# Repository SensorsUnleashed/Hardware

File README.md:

# Sensors unleashed Hardware

This repository will hold all the hardware for the sensors unleashed project.
All repositories will be placed here as submodules, which you can request
by a simple command:

git submodule update --init submoduleName

e.g.
git submodule update --init zb3219PA_XBEEAdapter

or for all submodules in the repo do:
git submodule update --init

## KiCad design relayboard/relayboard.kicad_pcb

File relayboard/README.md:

# relayboard

Simple board that is powered by both mains and a button cell battery.

It is able to:
* Operate a Single Pole Double Throw relay
* Has an i2c eeprom
* Can attach to a Sensors Unleashed radio module
* If mains is lost, the relay will release, but the radio will still be operating. This means that messages can still be send even though power is removed.

This board has many uses, but some ideas could be:
Use any installation in the house as input for the system. This device will detect if mains is on or off, and send messages as instructed. Perhaps turning on/off lamps or plugs in another location in a house.

The relay can be used to switch anything - lights, pumps, home appliances and so on.

Below you can see the prototype board.

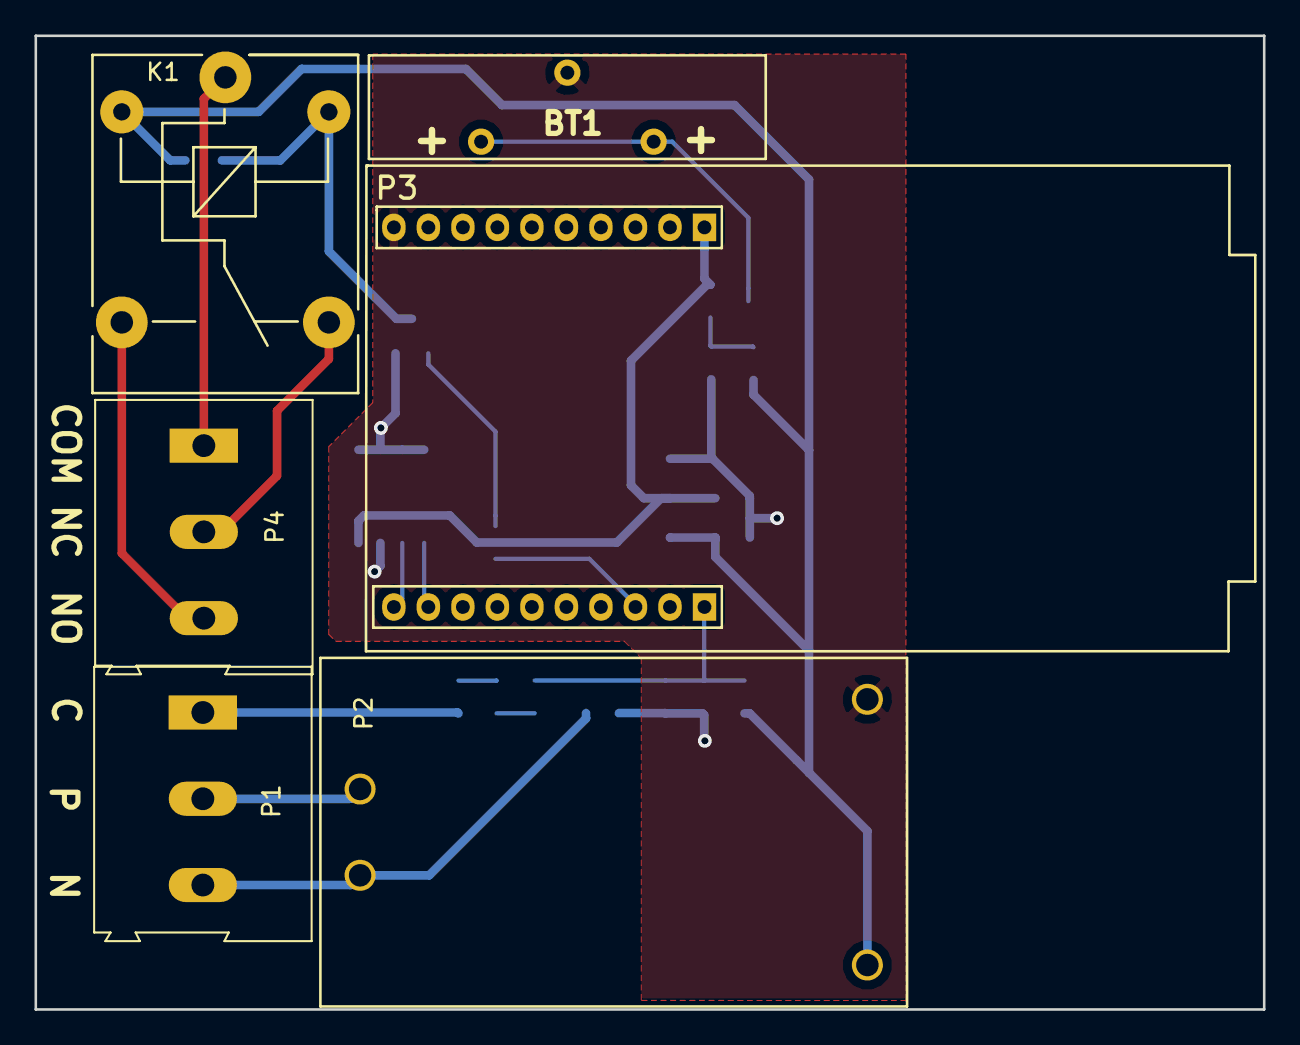
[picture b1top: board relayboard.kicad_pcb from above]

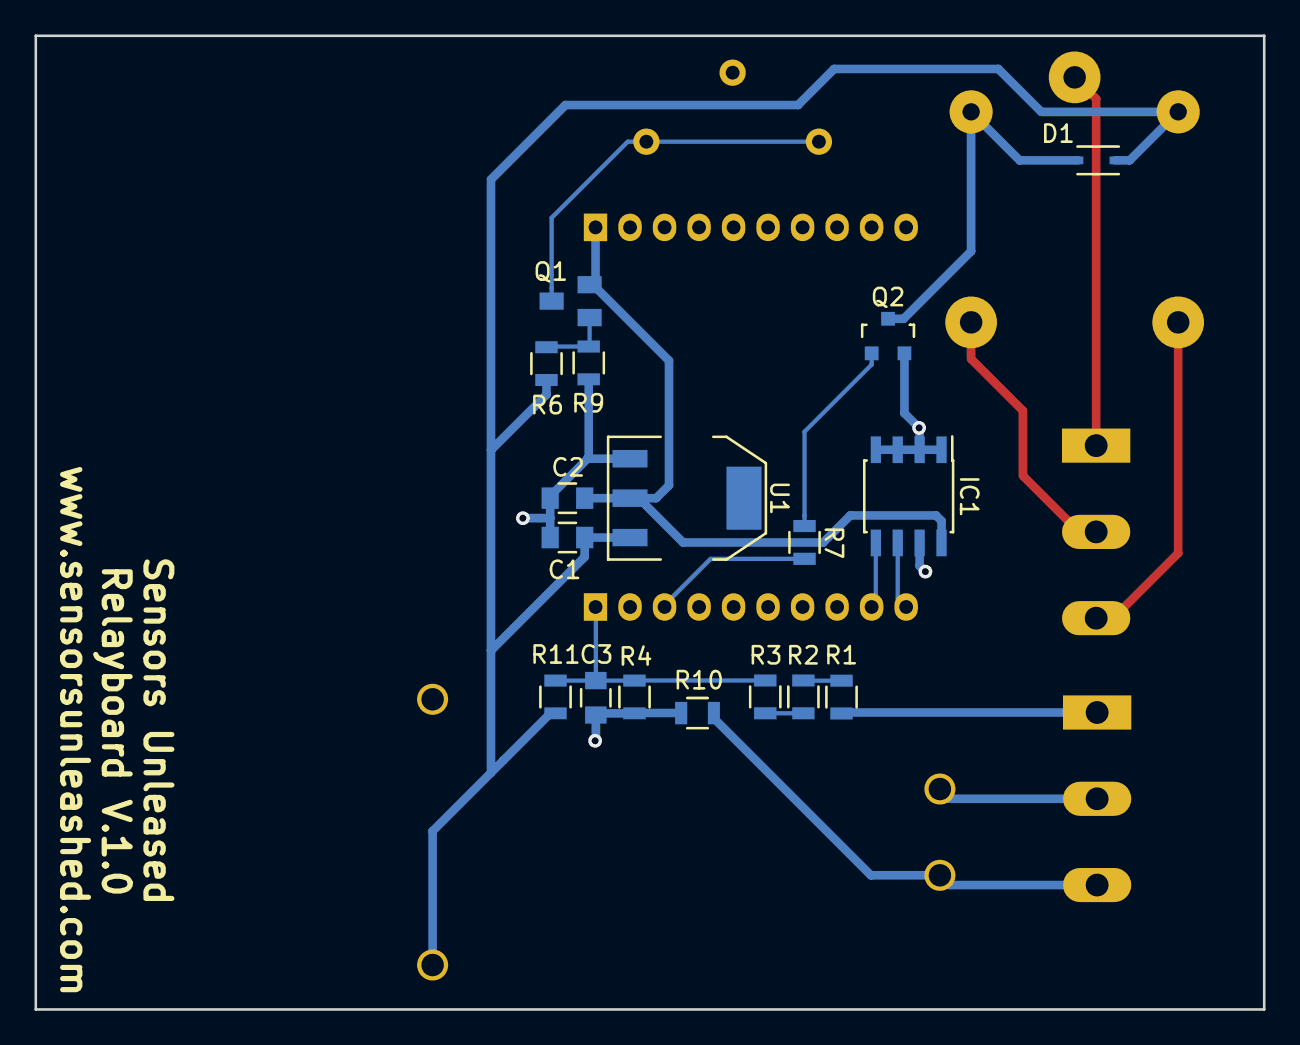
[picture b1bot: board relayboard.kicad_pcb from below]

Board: 2 copper layers, 71.2 x 56.4 mm, 23 parts (17 on the bottom side), 19 nets.

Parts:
BT1: CR2032; BATT_CR2032_VERT
C1: 100nF; C_0805
C2: 22uF; C_0805
C3: 1nF; C_0805
D1: BAS321; SOD-323
IC1: AT24C256C-SSHL-T; SOIC-8_3.9x4.9mm_Pitch1.27mm
K1: RELAY_1RT; Relay_SRD_XVDC-SL-C_Series
P1: Supply; AK300-3
P2: HLK-PM01
P3: Sensors Unleashed Radio; zb3219PA_radio
P4: Relay; AK300-3
Q1: FDN304P; SSOT-3
Q2: BC849; SOT-23
R1, R2, R3: 330k; R_0805
R4: 6040R; R_0805
R6: 100R; R_0805
R7: 2k; R_0805
R9: 100k; R_0805
R10: 0R; R_0805
R11: 12835R; R_0805
U1: AMS1117; SOT-223

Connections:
+BATT: BT1.1, Q1.3
/Control: P1.1, R1.2
/Nul: P1.3, P2.2, R10.2
/Phase: P1.2, P2.1
GND: BT1.2, C1.2, C2.2, C3.2, IC1.1, IC1.2, IC1.3, IC1.4, IC1.7, P2.3, P3.10, Q2.2, R4.2, R9.2, R10.1, U1.1
I2C_SCL: IC1.6, P3.11
I2C_SDA: IC1.5, P3.12
Mainsdetect: C3.1, P3.20, R3.1, R4.1, R11.2
unnamed: K1.1, P4.3
unnamed: K1.2, P4.1
unnamed: K1.3, P4.2
unnamed: Q1.1, R6.2, R9.1
unnamed: Q2.1, R7.2
unnamed: R1.1, R2.2
unnamed: R2.1, R3.2
Relay: P3.18, R7.1
Relay1: D1.2, K1.4, Q2.3
Relay2: C1.1, D1.1, K1.5, P2.4, R6.1, R11.1, U1.3
VCC: C2.1, IC1.8, P3.1, Q1.2, U1.2

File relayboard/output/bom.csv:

"Reference"; "Quantity"; "Value"; "Footprint"; "Datasheet"; "Characteristics"; "Package ID"; "Supplier"; "Manufacturer Name"; "Manufacturer Part Number"; "Supplier Order number"; "Description"; "Alt Manufacturer Name"; "Notes"
"BT1";"1";"CR2032";"SensorsUnleashed:BATT_CR2032_VERT";"https://www.aliexpress.com/item/Binmer-New-Vertical-CR2032-2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";"Coin, 20.0mm";"Throughole, Holder (Open)";"Aliexpress";;;;"Coin Cell, Holder";;
"C1";"1";"100nF";"Capacitors_SMD:C_0805";"";"25 V, X7R";"0805";"digi key";"AVX Corporation";"08053C104KAT2A";"478-3755-1-ND";;;
"C2";"1";"22uF";"Capacitors_SMD:C_0805";"http://datasheets.avx.com/F98.pdf";"Tantalum, ESR 4Ohm, 10V, 20%";"0805";"Digikey";"AVX Corporation";"F981A226MSA";"478-8649-1-ND";;;
"C3";"1";"1nF";"Capacitors_SMD:C_0805";"http://datasheets.avx.com/X7RDielectric.pdf";"50V, X7R";"0805";"Digikey";"AVX Corporation";"08055C102KAT2A";"478-1371-1-ND";;;
"D1";"1";"BAS321";"Diodes_SMD:SOD-323";"http://www.nxp.com/documents/data_sheet/BAS321.pdf";"Vr=200V, Io=250mA, Vf=1.25V@200mA";"SOD-323";"Digi Key";"NXP Semiconductors";"BAS321,115";"568-6002-1-ND";"Fast Recovery Rectifiers";;
"IC1";"1";"AT24C256C-SSHL-T";"Housings_SOIC:SOIC-8_3.9x4.9mm_Pitch1.27mm";"http://www.atmel.com/images/atmel-8568-seeprom-at24c256c-dat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";"256K (32K x 8) eeprom, i2c";"8-SOIC";"Aliexpress";;;"https://www.aliexpress.com/item/Free-shipping-10pcs-lot-AT24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";;;
"K1";"1";"RELAY_1RT";"SensorsUnleashed:Relay_SRD_XVDC-SL-C_Series";"";;;"Aliexpress";;;;;;
"P1";"1";"Supply";"Connect:AK300-3";""
"P2";"1";"HLK-PM01";"SensorsUnleashed:HLK-PM01";"https://www.aliexpress.com/item/5pcs-TSP-05-replace-HLK-PM01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";"100-240VAC in, 5VDC/3W out";;"Aliexpress";;;;;;"Meets CE and UL; written, but not proven!"
"P3";"1";"Sensors Unleashed Radio";"SensorsUnleashed:zb3219PA_radio";""
"P4";"1";"Relay";"Connect:AK300-3";""
"Q1";"1";"FDN304P";"SensorsUnleashed:SSOT-3";"https://www.fairchildsemi.com/datasheets/FD/FDN304P.pdf";"20V 2.4A";"SSOT3";"Digikey";"Fairchild Semiconductor";"FDN304P";;"MOSFET P-CH";"FDN304PCT-ND";
"Q2";"1";"BC849";"TO_SOT_Packages_SMD:SOT-23";"http://www.mccsemi.com/up_pdf/BC846A-BC849C(SOT-23).pdf";;"SOT23";"Digikey";"Micro Commercial Co";"BC849C-TP";"BC849C-TPMSCT-ND";"TRANS NPN 30V 0.1A";;
"R1, R2, R3";"3";"330k";"Resistors_SMD:R_0805";"https://industrial.panasonic.com/ww/products/resistors/chip-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";"1%,";"0805";;;;;;;
"R10";"1";"0R";"Resistors_SMD:R_0805";"";"1%";"0805";;;;;;;
"R11";"1";"12835R";"Resistors_SMD:R_0805";"";"1%";"0805";;;;;;;
"R4";"1";"6040R";"Resistors_SMD:R_0805";"";"1%";"0805";;;;;;;
"R6";"1";"100R";"Resistors_SMD:R_0805";"";"1%";"0805";;;;;;;
"R7";"1";"2k";"Resistors_SMD:R_0805";"";"1%";"0805";;;;;;;
"R9";"1";"100k";"Resistors_SMD:R_0805";"";"1%";"0805";;;;;;;
"U1";"1";"AMS1117";"TO_SOT_Packages_SMD:SOT-223";"";"Fixed 3.3V, 1A";"SOT-223";;"Advanced Monolithic Systems";"AMS1117-3.3";;;;

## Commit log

2016-11-25 Added the zb3219PA adapter module to the repository
2016-11-25 Changed the Readme
2016-11-25 Added the submodule info.
2016-11-25 Added the command needed for checkout the submodules in this repo
2016-11-25 Track the master branch
2016-11-25 Added the kicad components as a submodule
2016-12-05 Added the relayboard
2017-03-06 Added RadioOne as a submodule
2017-03-06 Updated components
2017-03-06 Added pulse counter board
2017-03-06 Removed old relayboard
2017-03-07 Resized the images to be webfriendly
2017-03-07 Removed submodule relauboard
2017-03-07 Added a relay module
2017-03-07 Remove relay board - should be added as a module
2017-03-07 Removed relayboard again
2017-03-07 Added relayboard again again
2017-03-14 Updated RadioOne with schematics and updated bom
2017-03-14 Updated hardware links
2017-03-14 Updated relayboard repo
2017-03-29 Various updates
